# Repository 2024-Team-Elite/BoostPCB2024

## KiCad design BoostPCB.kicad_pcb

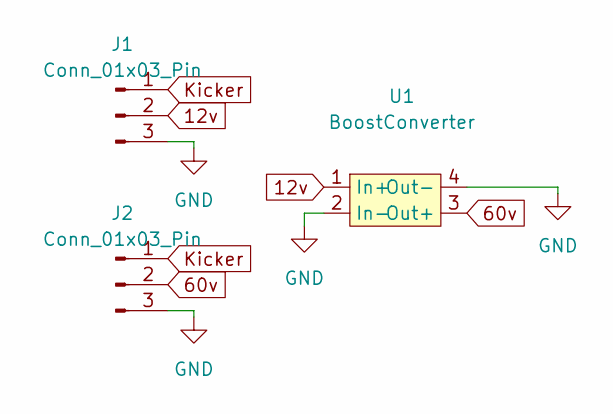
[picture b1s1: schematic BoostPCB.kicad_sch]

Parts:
J1, J2: Conn_01x03_Pin; JST_XH_B3B-XH-AM_1x03_P2.50mm_Vertical
U1: BoostConverter; Boost_Convertor_LM2577

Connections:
12v: J1.2, U1.1 (In+)
60v: J2.2, U1.3 (Out+)
GND: J1.3, J2.3, U1.2 (In-), U1.4 (Out-)
Kicker: J1.1, J2.1

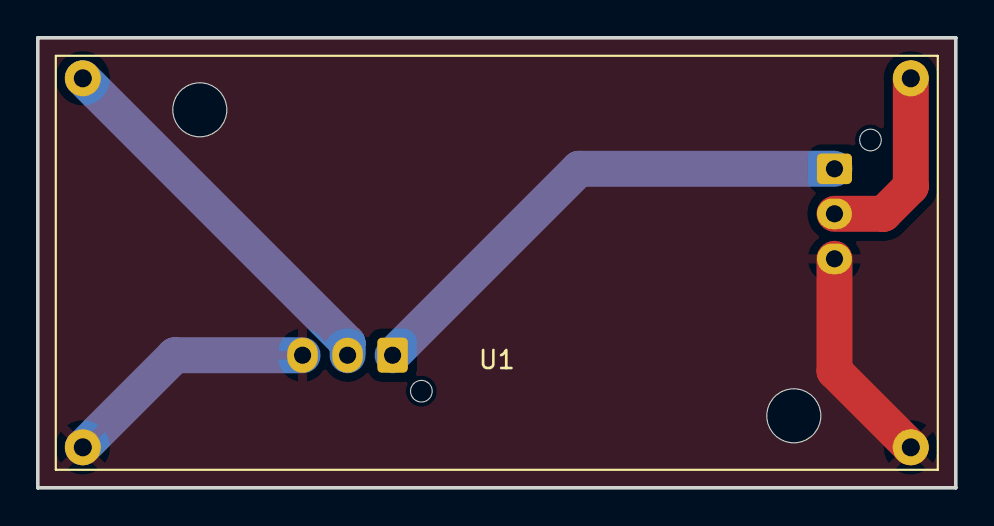
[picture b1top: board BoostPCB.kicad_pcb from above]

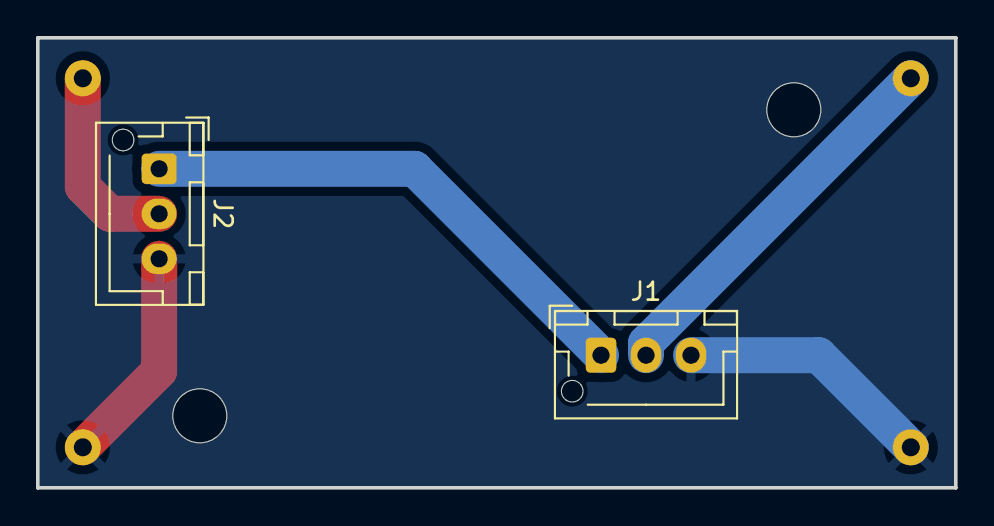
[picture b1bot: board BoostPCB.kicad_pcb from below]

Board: 2 copper layers, 51.0 x 25.0 mm, 3 parts (2 on the bottom side), 4 nets.

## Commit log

2024-03-03 finished
2024-03-08 Fixed connector side
2024-03-10 Done
2024-04-21 Capacitor Moving
    Caps no longer intersect with main PCB
